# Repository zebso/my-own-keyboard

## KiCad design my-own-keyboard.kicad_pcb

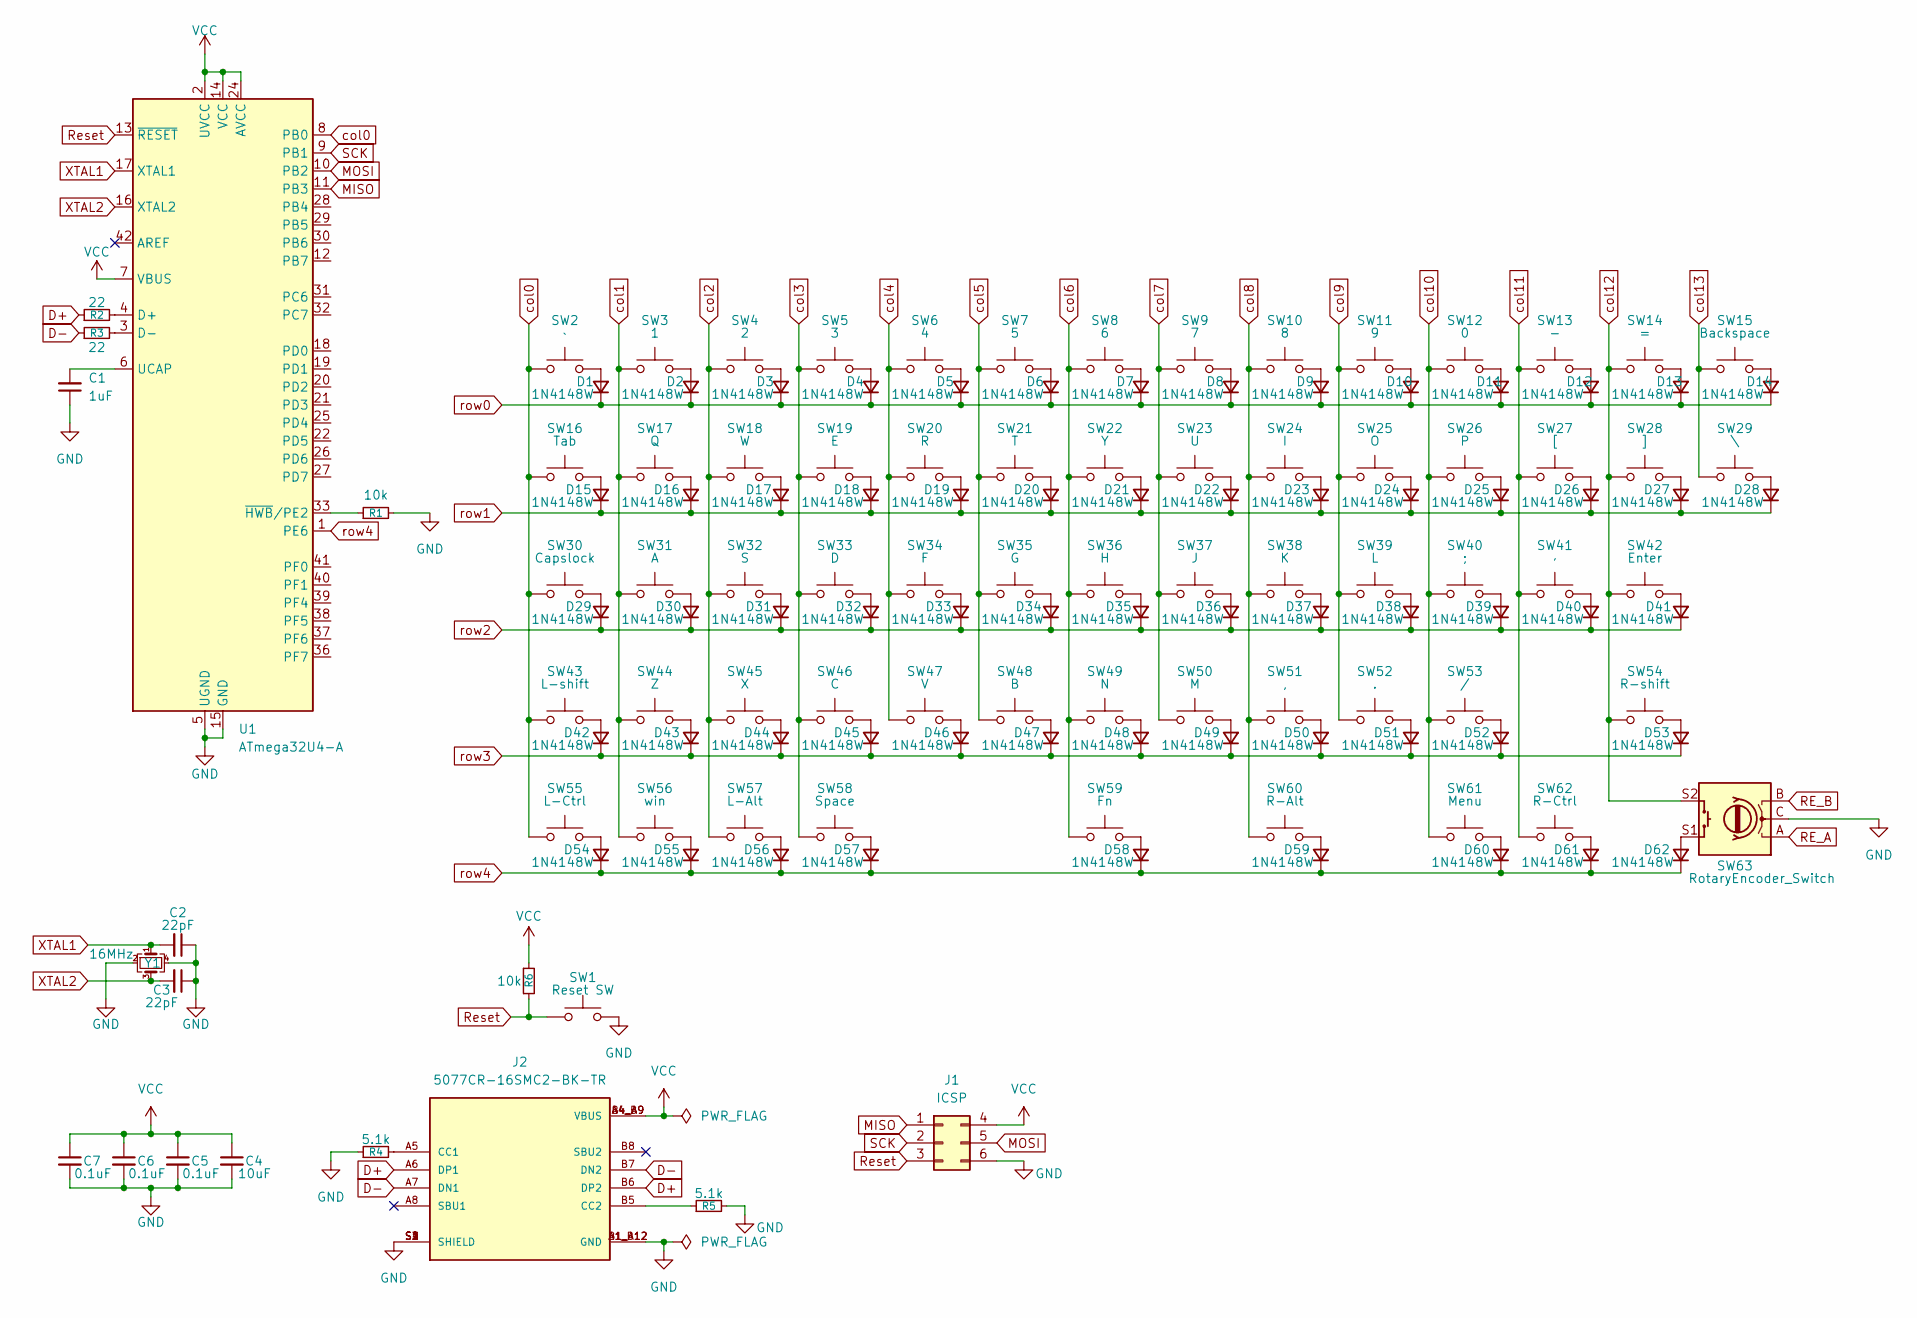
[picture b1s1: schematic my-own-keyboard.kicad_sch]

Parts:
C1: 1uF; C_0603_1608Metric
C2, C3: 22pF; C_0603_1608Metric
C4: 10uF; C_0603_1608Metric
C5, C6, C7: 0.1uF; C_0603_1608Metric
D1, D2, D3, D4, D5, D6, D7, D8, D9, D10, D11, D12, D13, D14, D15, D16, D17, D18, D19, D20, D21, D22, D23, D24, D25, D26, D27, D28, D29, D30, D31, D32, D33, D34, D35, D36, D37, D38, D39, D40, D41, D42, D43, D44, D45, D46, D47, D48, D49, D50, D51, D52, D53, D54, D55, D56, D57, D58, D59, D60, D61, D62: 1N4148W; D3_TH_SMD
J1: ICSP; PinSocket_2x03_P1.27mm_Vertical
J2: 5077CR-16SMC2-BK-TR; Usb_C_NELTRON_5077CR-16SMC2-BK-TR; PARTREV B
R1, R6: 10k; R_0603_1608Metric
R2, R3: 22; R_0603_1608Metric
R4, R5: 5.1k; R_0603_1608Metric
SW1: Reset SW; ResetSW TSHA-T-2.5B2-19SH
SW2: `; CherryMX_Hotswap_via_1U
SW3: 1; CherryMX_Hotswap_via_1U
SW4: 2; CherryMX_Hotswap_via_1U
SW5: 3; CherryMX_Hotswap_via_1U
SW6: 4; CherryMX_Hotswap_via_1U
SW7: 5; CherryMX_Hotswap_via_1U
SW8: 6; CherryMX_Hotswap_via_1U
SW9: 7; CherryMX_Hotswap_via_1U
SW10: 8; CherryMX_Hotswap_via_1U
SW11: 9; CherryMX_Hotswap_via_1U
SW12: 0; CherryMX_Hotswap_via_1U
SW13: -; CherryMX_Hotswap_via_1U
SW14: =; CherryMX_Hotswap_via_1U
SW15: Backspace; CherryMX_Hotswap_via_2U
SW16: Tab; CherryMX_Hotswap_via_1.5U
SW17: Q; CherryMX_Hotswap_via_1U
SW18: W; CherryMX_Hotswap_via_1U
SW19: E; CherryMX_Hotswap_via_1U
SW20: R; CherryMX_Hotswap_via_1U
SW21: T; CherryMX_Hotswap_via_1U
SW22: Y; CherryMX_Hotswap_via_1U
SW23: U; CherryMX_Hotswap_via_1U
SW24: I; CherryMX_Hotswap_via_1U
SW25: O; CherryMX_Hotswap_via_1U
SW26: P; CherryMX_Hotswap_via_1U
SW27: [; CherryMX_Hotswap_via_1U
SW28: ]; CherryMX_Hotswap_via_1U
SW29: \; CherryMX_Hotswap_via_1.5U
SW30: Capslock; CherryMX_Hotswap_via_1.75U
SW31: A; CherryMX_Hotswap_via_1U
SW32: S; CherryMX_Hotswap_via_1U
SW33: D; CherryMX_Hotswap_via_1U
SW34: F; CherryMX_Hotswap_via_1U
SW35: G; CherryMX_Hotswap_via_1U
SW36: H; CherryMX_Hotswap_via_1U
SW37: J; CherryMX_Hotswap_via_1U
SW38: K; CherryMX_Hotswap_via_1U
SW39: L; CherryMX_Hotswap_via_1U
SW40: ;; CherryMX_Hotswap_via_1U
SW41: '; CherryMX_Hotswap_via_1U
SW42: Enter; CherryMX_Hotswap_via_2.25U
SW43: L-shift; CherryMX_Hotswap_via_2.25U
SW44: Z; CherryMX_Hotswap_via_1U
SW45: X; CherryMX_Hotswap_via_1U
SW46: C; CherryMX_Hotswap_via_1U
SW47: V; CherryMX_Hotswap_via_1U
SW48: B; CherryMX_Hotswap_via_1U
SW49: N; CherryMX_Hotswap_via_1U
SW50: M; CherryMX_Hotswap_via_1U
SW51: ,; CherryMX_Hotswap_via_1U
SW52: .; CherryMX_Hotswap_via_1U
SW53: /; CherryMX_Hotswap_via_1U
SW54: R-shift; CherryMX_Hotswap_via_2.75U
SW55: L-Ctrl; CherryMX_Hotswap_via_1.25U
SW56: win; CherryMX_Hotswap_via_1.25U
SW57: L-Alt; CherryMX_Hotswap_via_1.25U
SW58: Space; CherryMX_Hotswap_via_3U
SW59: Fn; CherryMX_Hotswap_via_3U
SW60: R-Alt; CherryMX_Hotswap_via_1.25U
SW61: Menu; CherryMX_Hotswap_via_1.25U
SW62: R-Ctrl; CherryMX_Hotswap_via_1.25U
SW63: RotaryEncoder_Switch; RotaryEncoder_Alps_EC12E-Switch_Vertical_H20mm
U1: ATmega32U4-A; TQFP-44_10x10mm_P0.8mm
Y1: 16MHz; Crystal_SMD_3225-4Pin_3.2x2.5mm

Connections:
D+: J2.A6 (DP1), J2.B6 (DP2), R2.1
D-: J2.A7 (DN1), J2.B7 (DN2), R3.1
GND: C1.1, C2.1, C3.1, C4.2, C5.2, C6.2, C7.2, J1.6, J2.A1_B12 (GND), J2.B1_A12 (GND), J2.S1 (SHIELD), J2.S2 (SHIELD), J2.S3 (SHIELD), J2.S4 (SHIELD), R1.2, R4.1, R5.2, SW1.2, SW63.C, U1.5 (UGND), U1.15 (GND), U1.23 (GND), U1.35 (GND), U1.43 (GND), Y1.2, Y1.4
MISO: J1.1, U1.11 (PB3)
MOSI: J1.5, U1.10 (PB2)
unnamed: D1.2 (A), SW2.2
unnamed: D2.2 (A), SW3.2
unnamed: D3.2 (A), SW4.2
unnamed: D4.2 (A), SW5.2
unnamed: D5.2 (A), SW6.2
unnamed: D6.2 (A), SW7.2
unnamed: D7.2 (A), SW8.2
unnamed: D8.2 (A), SW9.2
unnamed: D9.2 (A), SW10.2
unnamed: D10.2 (A), SW11.2
unnamed: D11.2 (A), SW12.2
unnamed: D12.2 (A), SW13.2
unnamed: D13.2 (A), SW14.2
unnamed: D14.2 (A), SW15.2
unnamed: D15.2 (A), SW16.2
unnamed: D16.2 (A), SW17.2
unnamed: D17.2 (A), SW18.2
unnamed: D18.2 (A), SW19.2
unnamed: D19.2 (A), SW20.2
unnamed: D20.2 (A), SW21.2
unnamed: D21.2 (A), SW22.2
unnamed: D22.2 (A), SW23.2
unnamed: D23.2 (A), SW24.2
unnamed: D24.2 (A), SW25.2
unnamed: D25.2 (A), SW26.2
unnamed: D26.2 (A), SW27.2
unnamed: D27.2 (A), SW28.2
unnamed: D28.2 (A), SW29.2
unnamed: D29.2 (A), SW30.2
unnamed: D30.2 (A), SW31.2
unnamed: D31.2 (A), SW32.2
unnamed: D32.2 (A), SW33.2
unnamed: D33.2 (A), SW34.2
unnamed: D34.2 (A), SW35.2
unnamed: D35.2 (A), SW36.2
unnamed: D36.2 (A), SW37.2
unnamed: D37.2 (A), SW38.2
unnamed: D38.2 (A), SW39.2
unnamed: D39.2 (A), SW40.2
unnamed: D40.2 (A), SW41.2
unnamed: D41.2 (A), SW42.2
unnamed: D42.2 (A), SW43.2
unnamed: D43.2 (A), SW44.2
unnamed: D44.2 (A), SW45.2
unnamed: D45.2 (A), SW46.2
unnamed: D46.2 (A), SW47.2
unnamed: D47.2 (A), SW48.2
unnamed: D48.2 (A), SW49.2
unnamed: D49.2 (A), SW50.2
unnamed: D50.2 (A), SW51.2
unnamed: D51.2 (A), SW52.2
unnamed: D52.2 (A), SW53.2
unnamed: D53.2 (A), SW54.2
unnamed: D54.2 (A), SW55.2
unnamed: D55.2 (A), SW56.2
unnamed: D56.2 (A), SW57.2
unnamed: D57.2 (A), SW58.2
unnamed: D58.2 (A), SW59.2
unnamed: D59.2 (A), SW60.2
unnamed: D60.2 (A), SW61.2
unnamed: D61.2 (A), SW62.2
unnamed: D62.2 (A), SW63.S1
unnamed: J2.A5 (CC1), R4.2
unnamed: J2.B5 (CC2), R5.1
unnamed: R2.2, U1.4 (D+)
unnamed: R3.2, U1.3 (D-)
unnamed: C1.2, U1.6 (UCAP)
unnamed: R1.1, U1.33 (~HWB/PE2)
RE_A: SW63.A
RE_B: SW63.B
Reset: J1.3, R6.2, SW1.1, U1.13 (~RESET)
SCK: J1.2, U1.9 (PB1)
VCC: C4.1, C5.1, C6.1, C7.1, J1.4, J2.A4_B9 (VBUS), J2.B4_A9 (VBUS), R6.1, U1.2 (UVCC), U1.7 (VBUS), U1.14 (VCC), U1.24 (AVCC), U1.34 (VCC), U1.44 (AVCC)
XTAL1: C2.2, U1.17 (XTAL1), Y1.1
XTAL2: C3.2, U1.16 (XTAL2), Y1.3
col0: SW2.1, SW16.1, SW30.1, SW43.1, SW55.1, U1.8 (PB0)
col1: SW3.1, SW17.1, SW31.1, SW44.1, SW56.1
col2: SW4.1, SW18.1, SW32.1, SW45.1, SW57.1
col3: SW5.1, SW19.1, SW33.1, SW46.1, SW58.1
col4: SW6.1, SW20.1, SW34.1, SW47.1
col5: SW7.1, SW21.1, SW35.1, SW48.1
col6: SW8.1, SW22.1, SW36.1, SW49.1, SW59.1
col7: SW9.1, SW23.1, SW37.1, SW50.1
col8: SW10.1, SW24.1, SW38.1, SW51.1, SW60.1
col9: SW11.1, SW25.1, SW39.1, SW52.1
col10: SW12.1, SW26.1, SW40.1, SW53.1, SW61.1
col11: SW13.1, SW27.1, SW41.1, SW62.1
col12: SW14.1, SW28.1, SW42.1, SW54.1, SW63.S2
col13: SW15.1, SW29.1
row0: D1.1 (K), D2.1 (K), D3.1 (K), D4.1 (K), D5.1 (K), D6.1 (K), D7.1 (K), D8.1 (K), D9.1 (K), D10.1 (K), D11.1 (K), D12.1 (K), D13.1 (K), D14.1 (K)
row1: D15.1 (K), D16.1 (K), D17.1 (K), D18.1 (K), D19.1 (K), D20.1 (K), D21.1 (K), D22.1 (K), D23.1 (K), D24.1 (K), D25.1 (K), D26.1 (K), D27.1 (K), D28.1 (K)
row2: D29.1 (K), D30.1 (K), D31.1 (K), D32.1 (K), D33.1 (K), D34.1 (K), D35.1 (K), D36.1 (K), D37.1 (K), D38.1 (K), D39.1 (K), D40.1 (K), D41.1 (K)
row3: D42.1 (K), D43.1 (K), D44.1 (K), D45.1 (K), D46.1 (K), D47.1 (K), D48.1 (K), D49.1 (K), D50.1 (K), D51.1 (K), D52.1 (K), D53.1 (K)
row4: D54.1 (K), D55.1 (K), D56.1 (K), D57.1 (K), D58.1 (K), D59.1 (K), D60.1 (K), D61.1 (K), D62.1 (K), U1.1 (PE6)

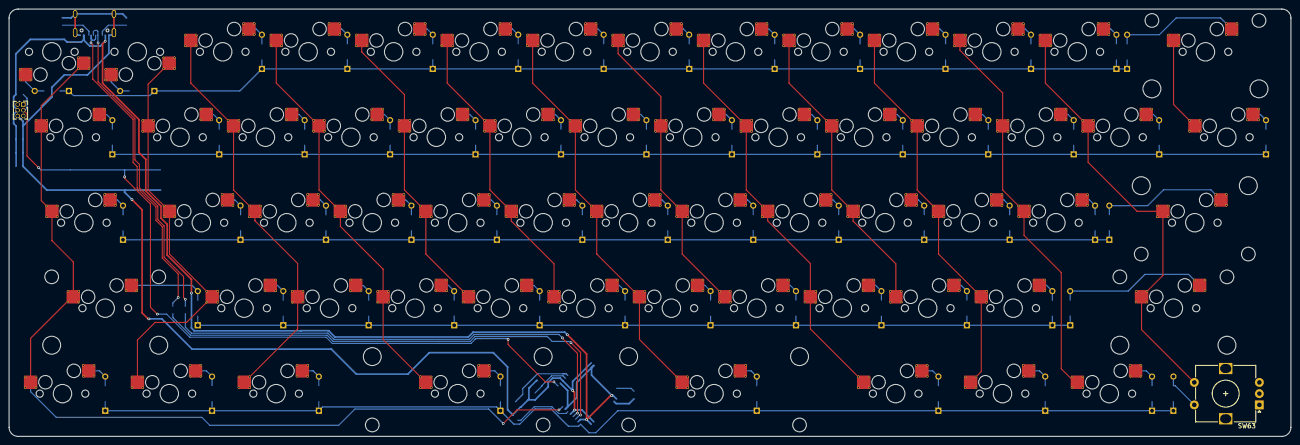
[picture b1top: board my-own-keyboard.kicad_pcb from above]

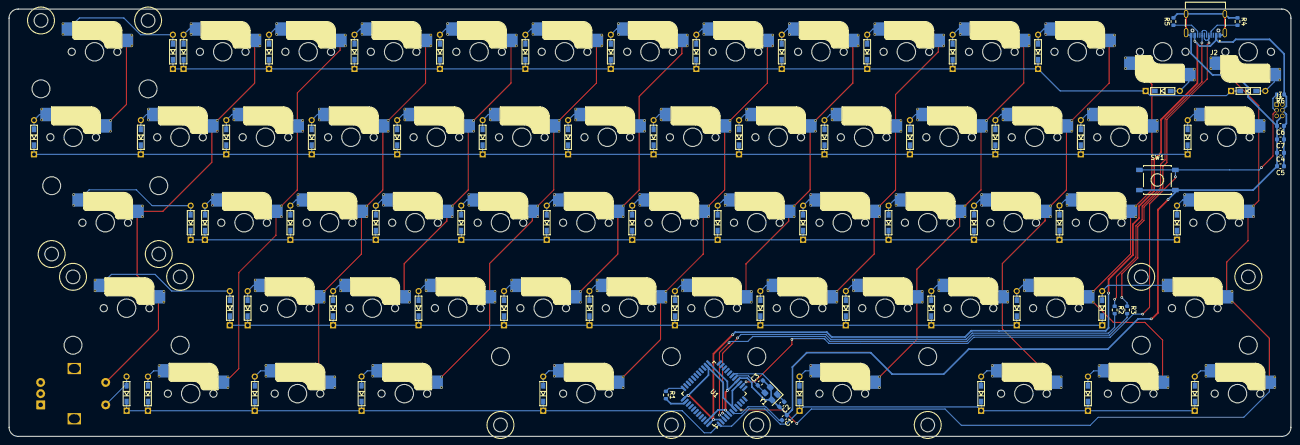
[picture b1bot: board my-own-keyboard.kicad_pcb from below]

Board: 2 copper layers, 285.8 x 95.2 mm, 142 parts (17 on the bottom side), 97 nets.

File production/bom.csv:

Designator,Footprint,Quantity,Value,LCSC Part #
C1,0603,1,1uF,
"C2, C3",0603,2,22pF,
C4,0603,1,10uF,
"C5, C6, C7",0603,3,0.1uF,
"D1, D10, D11, D12, D13, D14, D15, D16, D17, D18, D19, D2, D20, D21, D22, D23, D24, D25, D26, D27, D28, D29, D3, D30, D31, D32, D33, D34, D35, D36, D37, D38, D39, D4, D40, D41, D42, D43, D44, D45, D46, D47, D48, D49, D5, D50, D51, D52, D53, D54, D55, D56, D57, D58, D59, D6, D60, D61, D62, D7, D8, D9",D3_TH_SMD,62,1N4148W,
ICSP,PinSocket_2x03_P1.27mm_Vertical,1,ICSP,
J2,NELTRON_5077CR-16SMC2-BK-TR,1,5077CR-16SMC2-BK-TR,
"R1, R6",0603,2,10k,
"R2, R3",0603,2,22,
"R4, R5",0603,2,5.1k,
SW1,ResetSW,1,Reset SW,
SW10,CherryMX_Hotswap_via_1U,1,8,
SW11,CherryMX_Hotswap_via_1U,1,9,
SW12,CherryMX_Hotswap_via_1U,1,0,
SW13,CherryMX_Hotswap_via_1U,1,-,
SW14,CherryMX_Hotswap_via_1U,1,=,
SW15,CherryMX_Hotswap_via_2U,1,Backspace,
SW16,CherryMX_Hotswap_via_1.5U,1,Tab,
SW17,CherryMX_Hotswap_via_1U,1,Q,
SW18,CherryMX_Hotswap_via_1U,1,W,
SW19,CherryMX_Hotswap_via_1U,1,E,
SW2,CherryMX_Hotswap_via_1U,1,`,
SW20,CherryMX_Hotswap_via_1U,1,R,
SW21,CherryMX_Hotswap_via_1U,1,T,
SW22,CherryMX_Hotswap_via_1U,1,Y,
SW23,CherryMX_Hotswap_via_1U,1,U,
SW24,CherryMX_Hotswap_via_1U,1,I,
SW25,CherryMX_Hotswap_via_1U,1,O,
SW26,CherryMX_Hotswap_via_1U,1,P,
SW27,CherryMX_Hotswap_via_1U,1,[,
SW28,CherryMX_Hotswap_via_1U,1,],
SW29,CherryMX_Hotswap_via_1.5U,1,\,
SW3,CherryMX_Hotswap_via_1U,1,1,
SW30,CherryMX_Hotswap_via_1.75U,1,Capslock,
SW31,CherryMX_Hotswap_via_1U,1,A,
SW32,CherryMX_Hotswap_via_1U,1,S,
SW33,CherryMX_Hotswap_via_1U,1,D,
SW34,CherryMX_Hotswap_via_1U,1,F,
SW35,CherryMX_Hotswap_via_1U,1,G,
SW36,CherryMX_Hotswap_via_1U,1,H,
SW37,CherryMX_Hotswap_via_1U,1,J,
SW38,CherryMX_Hotswap_via_1U,1,K,
SW39,CherryMX_Hotswap_via_1U,1,L,
SW4,CherryMX_Hotswap_via_1U,1,2,
SW40,CherryMX_Hotswap_via_1U,1,;,
SW41,CherryMX_Hotswap_via_1U,1,',
SW42,CherryMX_Hotswap_via_2.25U,1,Enter,
SW43,CherryMX_Hotswap_via_2.25U,1,L-shift,
SW44,CherryMX_Hotswap_via_1U,1,Z,
SW45,CherryMX_Hotswap_via_1U,1,X,
SW46,CherryMX_Hotswap_via_1U,1,C,
SW47,CherryMX_Hotswap_via_1U,1,V,
SW48,CherryMX_Hotswap_via_1U,1,B,
SW49,CherryMX_Hotswap_via_1U,1,N,
SW5,CherryMX_Hotswap_via_1U,1,3,
SW50,CherryMX_Hotswap_via_1U,1,M,
SW51,CherryMX_Hotswap_via_1U,1,",",
SW52,CherryMX_Hotswap_via_1U,1,.,
SW53,CherryMX_Hotswap_via_1U,1,/,
SW54,CherryMX_Hotswap_via_2.75U,1,R-shift,
SW55,CherryMX_Hotswap_via_1.25U,1,L-Ctrl,
SW56,CherryMX_Hotswap_via_1.25U,1,win,
SW57,CherryMX_Hotswap_via_1.25U,1,L-Alt,
SW58,CherryMX_Hotswap_via_3U,1,Space,
SW59,CherryMX_Hotswap_via_3U,1,Fn,
SW6,CherryMX_Hotswap_via_1U,1,4,
SW60,CherryMX_Hotswap_via_1.25U,1,R-Alt,
SW61,CherryMX_Hotswap_via_1.25U,1,Menu,
SW62,CherryMX_Hotswap_via_1.25U,1,R-Ctrl,
SW63,RotaryEncoder_Alps_EC12E-Switch_Vertical_H20mm,1,RotaryEncoder_Switch,
SW7,CherryMX_Hotswap_via_1U,1,5,
SW8,CherryMX_Hotswap_via_1U,1,6,
SW9,CherryMX_Hotswap_via_1U,1,7,
U1,TQFP-44_10x10mm_P0.8mm,1,ATmega32U4-A,
Y1,Crystal_SMD_3225-4Pin_3.2x2.5mm,1,16MHz,

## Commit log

2025-08-11 created a KiCad project and add KiCad libraries
2025-08-11 created the circuit
2025-08-12 completed creating the first circuit
2025-08-12 added a rotary encoder
2025-08-12 put the footprints and defined the design rules
2025-08-13 wired
2025-08-13 completed wiring
2025-08-13 added ICSP
2025-08-13 completed all of the design of the PCB
2025-08-13 created the holes
2025-08-15 updated the pcb
2025-08-15 updated the directory
2025-08-15 wared
